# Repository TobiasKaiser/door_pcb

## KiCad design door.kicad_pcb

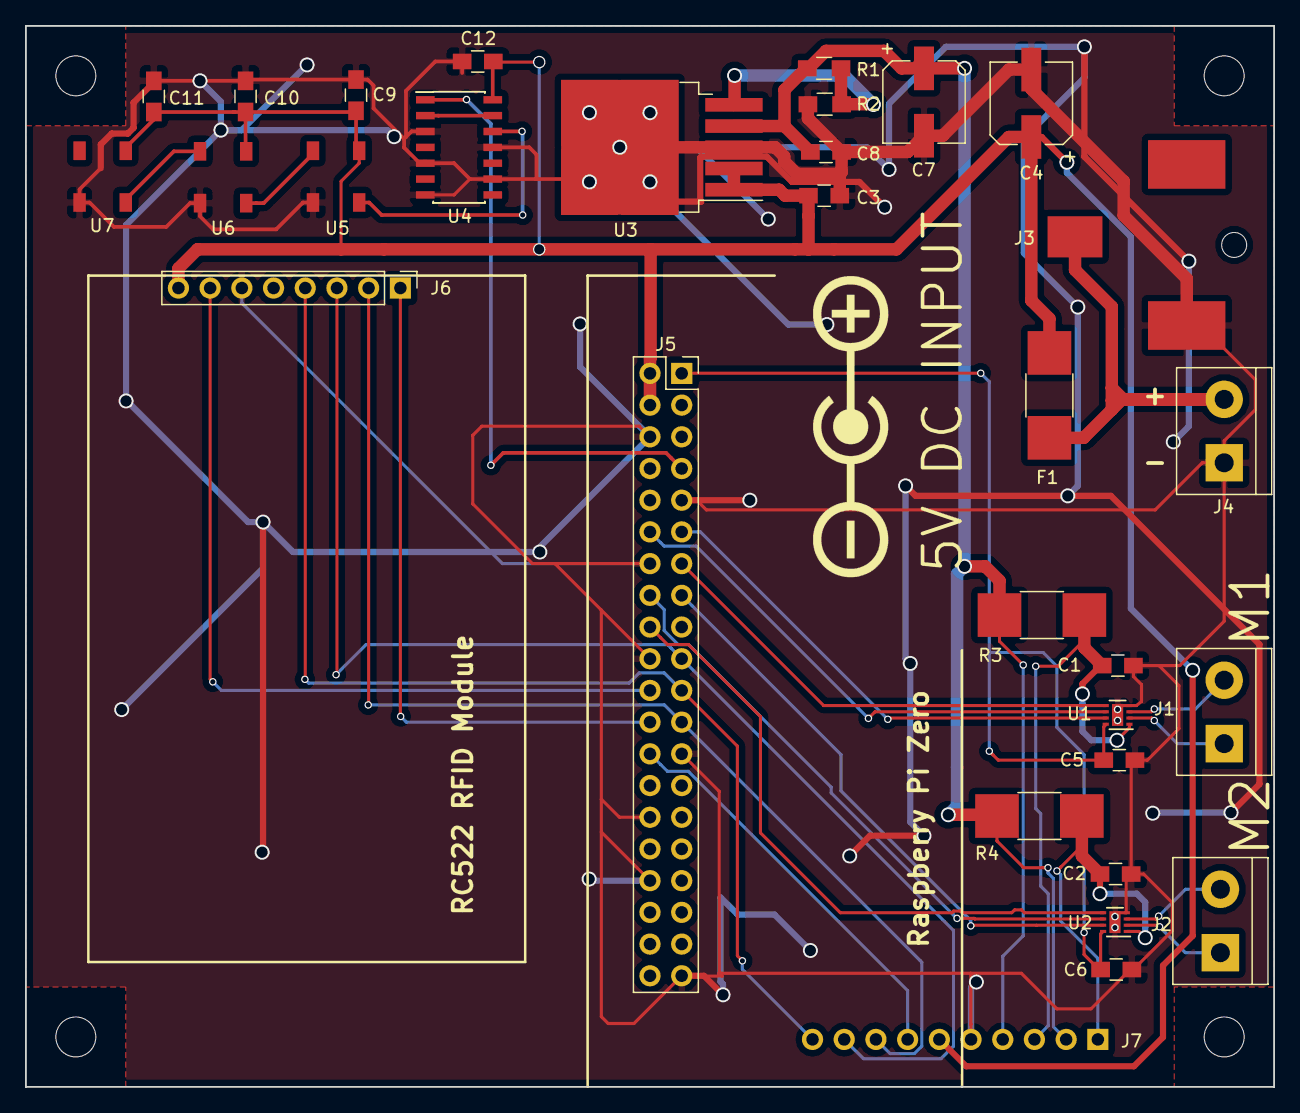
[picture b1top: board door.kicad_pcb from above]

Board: 2 copper layers, 100.0 x 85.0 mm, 31 parts (1 on the bottom side), 29 nets.

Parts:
C1, C2, C3, C5, C6, C8, C9, C10, C11, C12: 100n; C_0805_HandSoldering
C4, C7: 68u; CP_Elec_6.3x5.7
F1: Fuse; R_1812_HandSoldering
J1: Motor 1; TerminalBlock_bornier-2_P5.08mm
J2: Motor 2; TerminalBlock_bornier-2_P5.08mm
J3: POWER; PJ-036AH
J4: POWER; TerminalBlock_bornier-2_P5.08mm
J5: Raspberry Pi Zero; Socket_Strip_Straight_2x20_Pitch2.54mm
J6: RC522 RFID Module; Pin_Header_Straight_1x08_Pitch2.54mm
J7: To current sense module; Pin_Header_Straight_1x10_Pitch2.54mm
R1: 330; R_0805_HandSoldering
R2: 200; R_0805_HandSoldering
R3, R4: 0; R_1812_HandSoldering
U1, U2: DRV8838; DFN-8-1EP_2x2mm_Pitch0.5mm_FIXED
U3: SPX29302; TO-263-5_TabPin3
U4: 74HCT04; SOIC-14_3.9x8.7mm_Pitch1.27mm
U5, U6, U7: WS2812B

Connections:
+3V3: C7.1, C8.1, J7.2, J7.4, R1.1, R3.1, R4.1, U3.4
+5V: C3.1, C4.1, C9.1, C10.1, C11.1, C12.2, F1.1, J5.2, J5.4, J6.8, J7.6, U3.1, U3.2, U4.14, U5.1, U6.1, U7.1
/3V3_RASPI: C5.2, C6.2, J5.1, U1.8, U2.8
/CE0: J5.24, J6.1
/CE1: J5.26, J7.7
/LED_DIN: J5.7, U4.1
/M1_EN: J5.13, U1.5
/M1_PH: J5.12, U1.6
/M1_nSLEEP: J5.11, U1.7
/M2_EN: J5.18, U2.5
/M2_PH: J5.16, U2.6
/M2_nSLEEP: J5.15, U2.7
/MISO: J5.21, J6.4, J7.10
/MOSI: J5.19, J6.3, J7.9
/RC522_RESET: J5.22, J6.7
/SCLK: J5.23, J6.2, J7.8
/m1_csl: C1.1, J7.3, R3.2, U1.1
/m2_csl: C2.1, J7.1, R4.2, U2.1
GND: C1.2, C2.2, C3.2, C4.2, C5.1, C6.1, C7.2, C8.2, C9.2, C10.2, C11.2, C12.1, J3.2, J4.1, J5.6, J5.9, J5.14, J5.20, J5.25, J5.30, J5.34, J5.39, J6.6, J7.5, R2.2, U1.4, U1.9, U2.4, U2.9, U3.3, U4.3, U4.5, U4.7, U4.9, U4.11, U5.3, U6.3, U7.3
unnamed: F1.2, J3.1, J4.2
unnamed: J1.1, U1.2
unnamed: J1.2, U1.3
unnamed: J2.1, U2.2
unnamed: J2.2, U2.3
unnamed: R1.2, R2.1, U3.5
unnamed: U4.12, U5.4
unnamed: U4.2, U4.13
unnamed: U5.2, U6.4
unnamed: U6.2, U7.4

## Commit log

2018-02-24 initial commit - almost done
2018-02-24 routing done
2018-02-24 almost done...
2018-02-26 added schmatic pdf
2018-02-26 fertig; PCBs bei seeedstudio bestellt
2018-08-27 added schematic pdf for later
